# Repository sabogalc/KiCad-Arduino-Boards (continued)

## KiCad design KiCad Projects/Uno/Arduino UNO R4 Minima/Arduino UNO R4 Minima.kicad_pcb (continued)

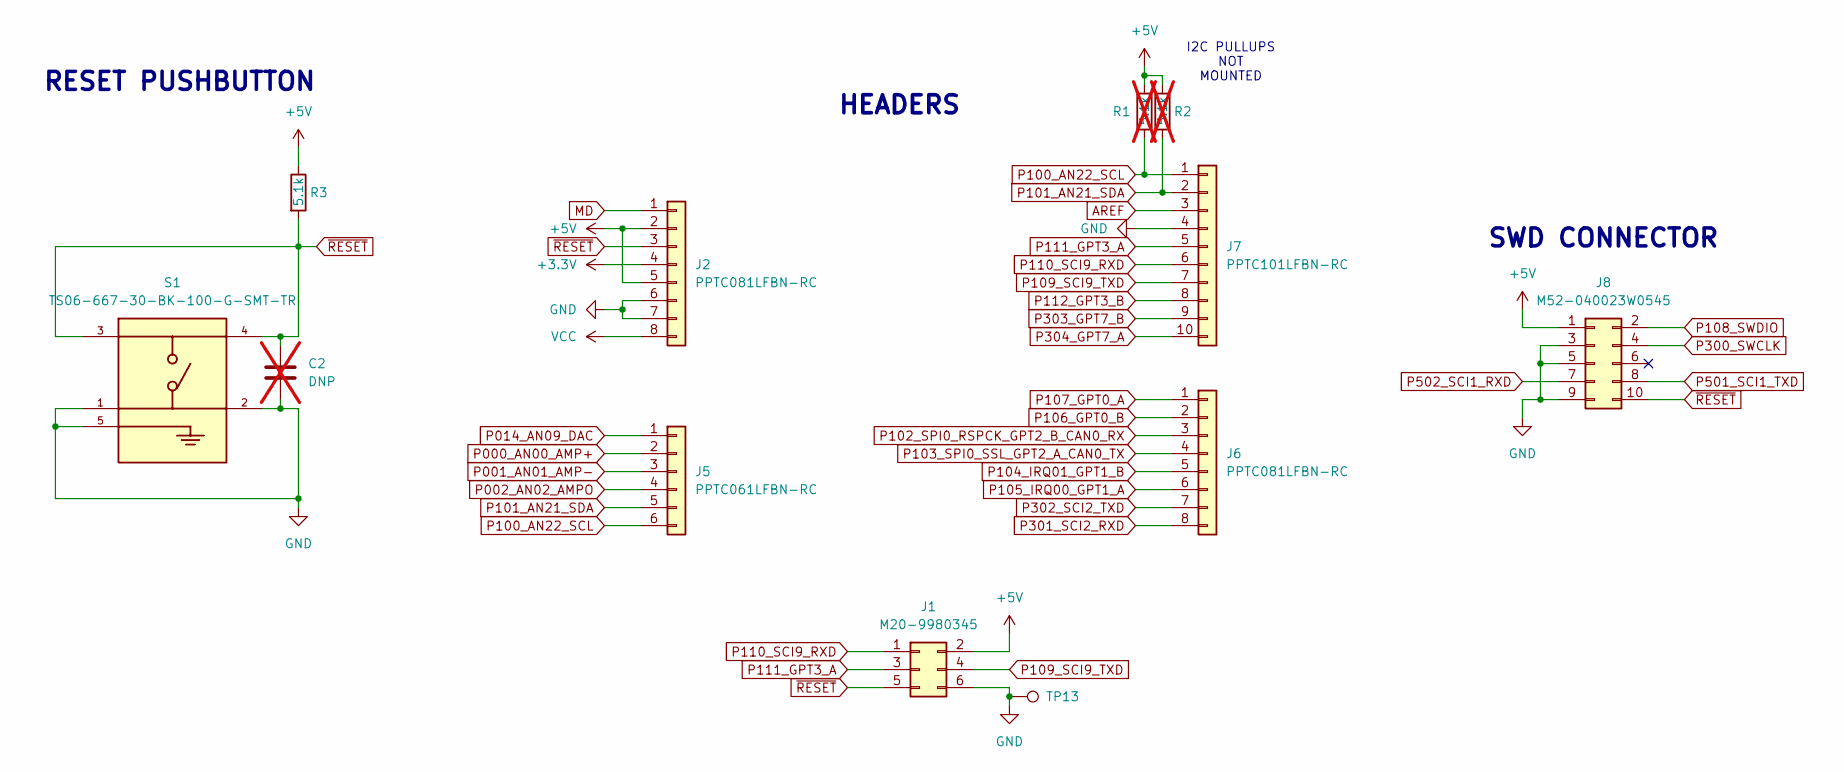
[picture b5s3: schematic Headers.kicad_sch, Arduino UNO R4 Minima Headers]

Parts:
C2: DNP; C_0402_1005Metric; not fitted
J1: M20-9980345; PinHeader_2x03_P2.54mm_Vertical
J2, J6: PPTC081LFBN-RC; PinSocket_1x08_P2.54mm_Vertical
J5: PPTC061LFBN-RC; PinSocket_1x06_P2.54mm_Vertical
J7: PPTC101LFBN-RC; PinSocket_1x10_P2.54mm_Vertical
J8: M52-040023W0545; PinHeader_2x05_P1.27mm_Vertical
R1, R2: 5.1k; R_0603_1608Metric; not fitted
R3: 5.1k; R_0402_1005Metric
S1: TS06-667-30-BK-100-G-SMT-TR; SW_TS06-667-30-BK-100-G-SMT-TR; PARTREV 1.0
TP13: TestPoint; TestPoint_Pad_D1.0mm

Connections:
+3.3V: J2.4; also elsewhere on the board
+5V: J1.2, J2.2, J2.5, J8.1, R1.1, R2.1, R3.1; also elsewhere on the board
AREF: J7.3; also elsewhere on the board
GND: C2.2, J1.6, J2.6, J2.7, J7.4, J8.3, J8.5, J8.9, S1.1, S1.2, S1.5, TP13.1; also elsewhere on the board
MD: J2.1; also elsewhere on the board
P000_AN00_AMP+: J5.2; also elsewhere on the board
P001_AN01_AMP-: J5.3; also elsewhere on the board
P002_AN02_AMPO: J5.4; also elsewhere on the board
P014_AN09_DAC: J5.1; also elsewhere on the board
P100_AN22_SCL: J5.6, J7.1, R1.2; also elsewhere on the board
P101_AN21_SDA: J5.5, J7.2, R2.2; also elsewhere on the board
P102_SPI0_RSPCK_GPT2_B_CAN0_RX: J6.3; also elsewhere on the board
P103_SPI0_SSL_GPT2_A_CAN0_TX: J6.4; also elsewhere on the board
P104_IRQ01_GPT1_B: J6.5; also elsewhere on the board
P105_IRQ00_GPT1_A: J6.6; also elsewhere on the board
P106_GPT0_B: J6.2; also elsewhere on the board
P107_GPT0_A: J6.1; also elsewhere on the board
P108_SWDIO: J8.2; also elsewhere on the board
P109_SCI9_TXD: J1.4, J7.7; also elsewhere on the board
P110_SCI9_RXD: J1.1, J7.6; also elsewhere on the board
P111_GPT3_A: J1.3, J7.5; also elsewhere on the board
P112_GPT3_B: J7.8; also elsewhere on the board
P300_SWCLK: J8.4; also elsewhere on the board
P301_SCI2_RXD: J6.8; also elsewhere on the board
P302_SCI2_TXD: J6.7; also elsewhere on the board
P303_GPT7_B: J7.9; also elsewhere on the board
P304_GPT7_A: J7.10; also elsewhere on the board
P501_SCI1_TXD: J8.8; also elsewhere on the board
P502_SCI1_RXD: J8.7; also elsewhere on the board
VCC: J2.8; also elsewhere on the board
~RESET: C2.1, J1.5, J2.3, J8.10, R3.2, S1.3, S1.4; also elsewhere on the board

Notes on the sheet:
RESET PUSHBUTTON
SWD CONNECTOR
HEADERS
I2C PULLUPS NOT MOUNTED

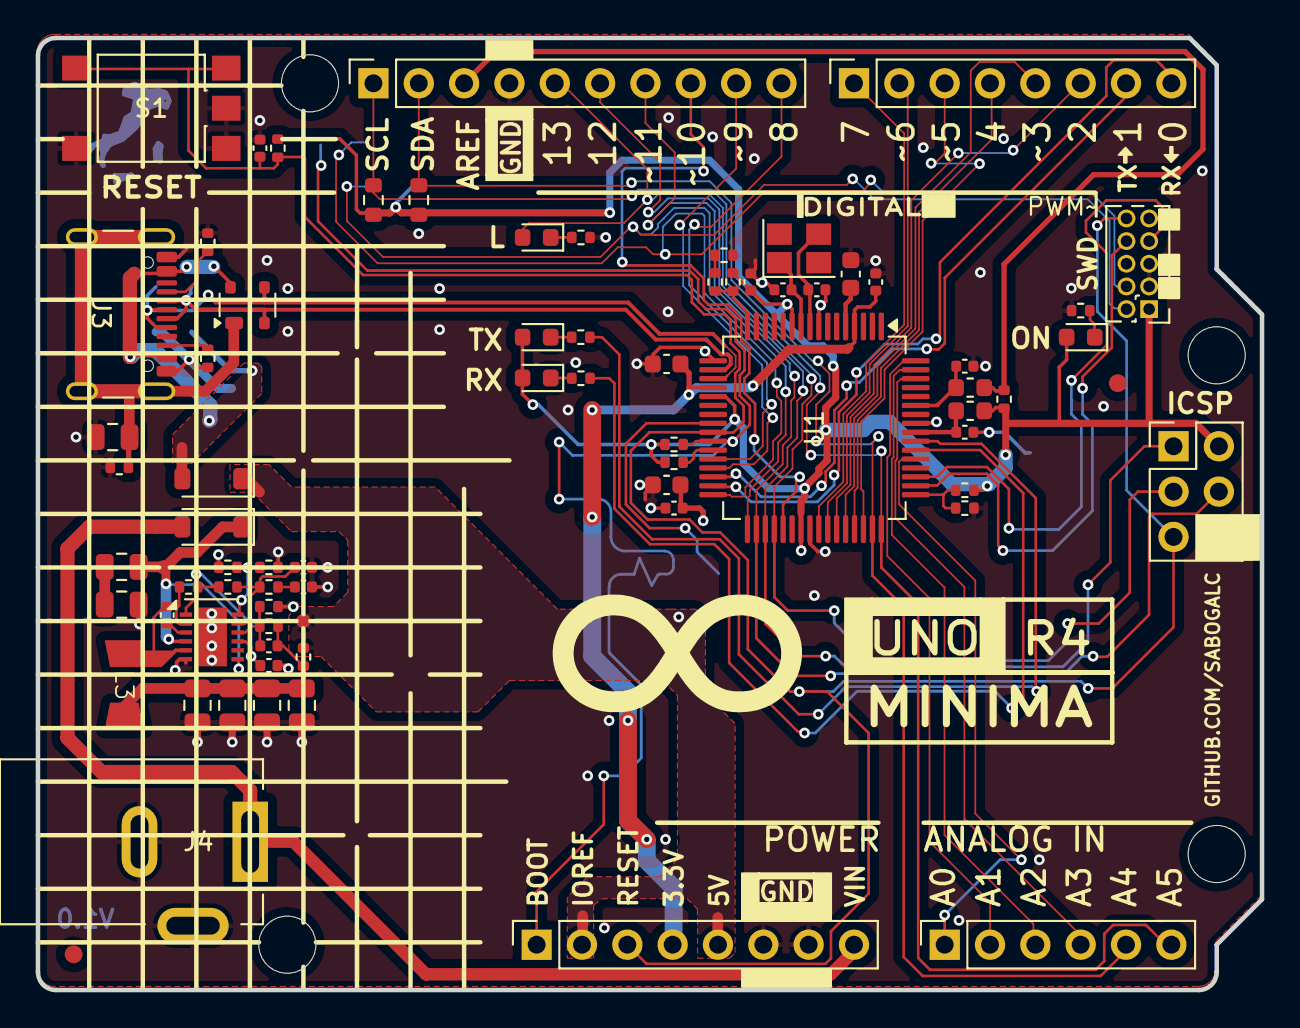
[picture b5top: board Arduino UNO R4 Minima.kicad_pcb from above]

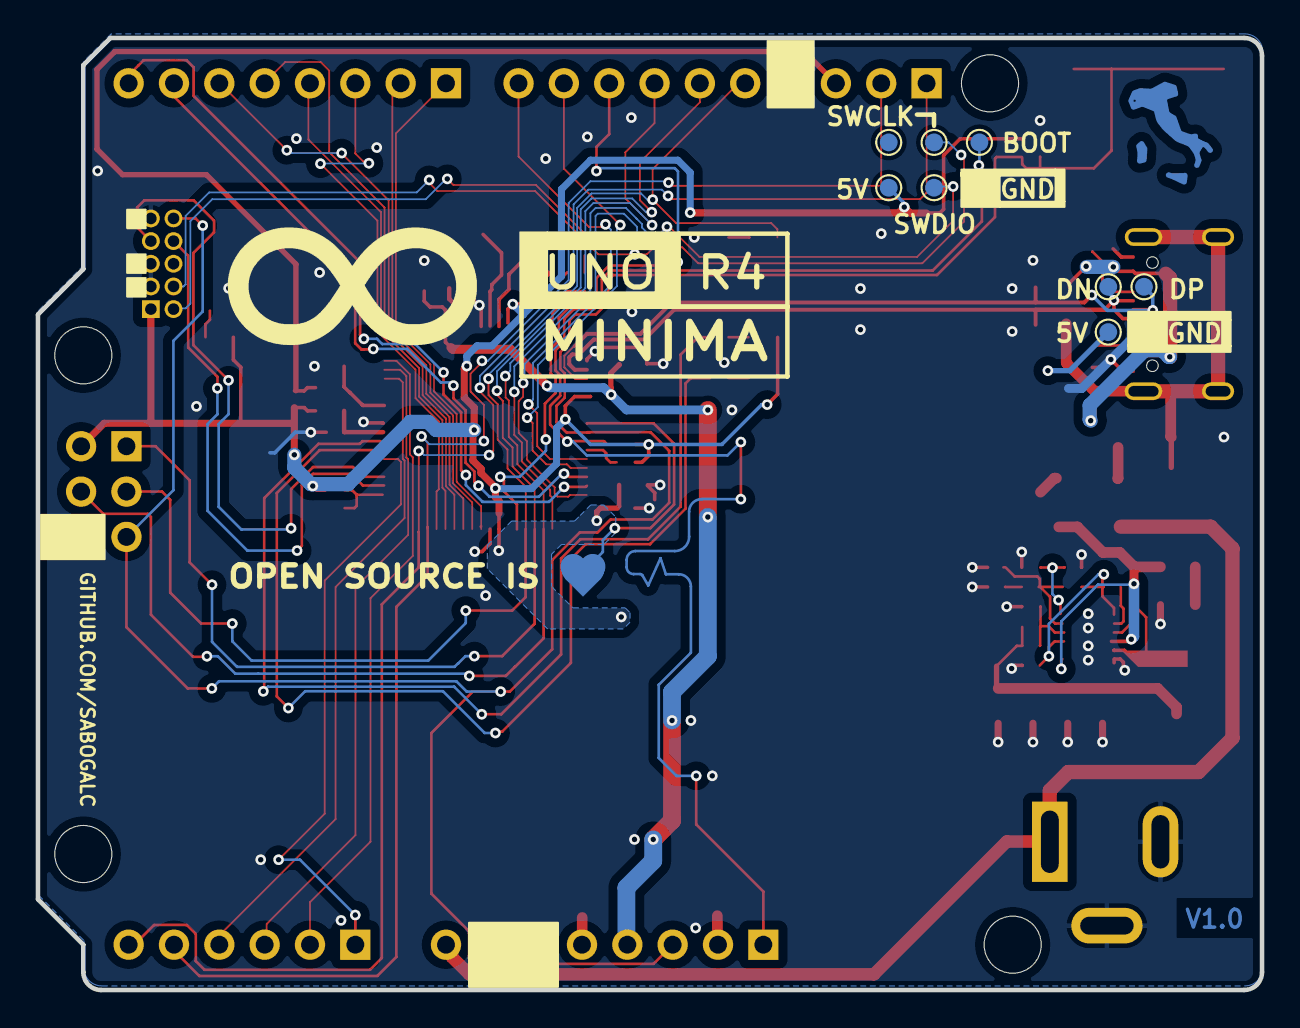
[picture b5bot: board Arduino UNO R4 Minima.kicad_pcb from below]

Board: 2 copper layers, 68.6 x 53.3 mm, 87 parts (11 on the bottom side), 64 nets.

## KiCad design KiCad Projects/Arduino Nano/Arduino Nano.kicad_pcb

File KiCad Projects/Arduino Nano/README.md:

# Nano

## Overview
The Nano is a compact and versatile board that surprisingly handles many of my existing projects designed for the UNO. Its small size makes it a great choice for projects where space is at a premium.

## Design Insights
This was the first board in this repository where I had to use a fully surface-mount USB-C connector instead of a through-hole variant. The original Nano also utilizes a surface-mount USB connector, as a through-hole option would interfere with routing and placement on the bottom layer.

While integrating the larger footprint of the USB-C connector, I had to adjust the silkscreen labels near the connector, but I ensured that all the necessary information remained clear and accessible.

## KiCad 3D View
Below are the screenshots of this board from KiCad's 3D board viewer.

## Real-World Application
Additionally, I have successfully built this board in real life and confirmed that it works.

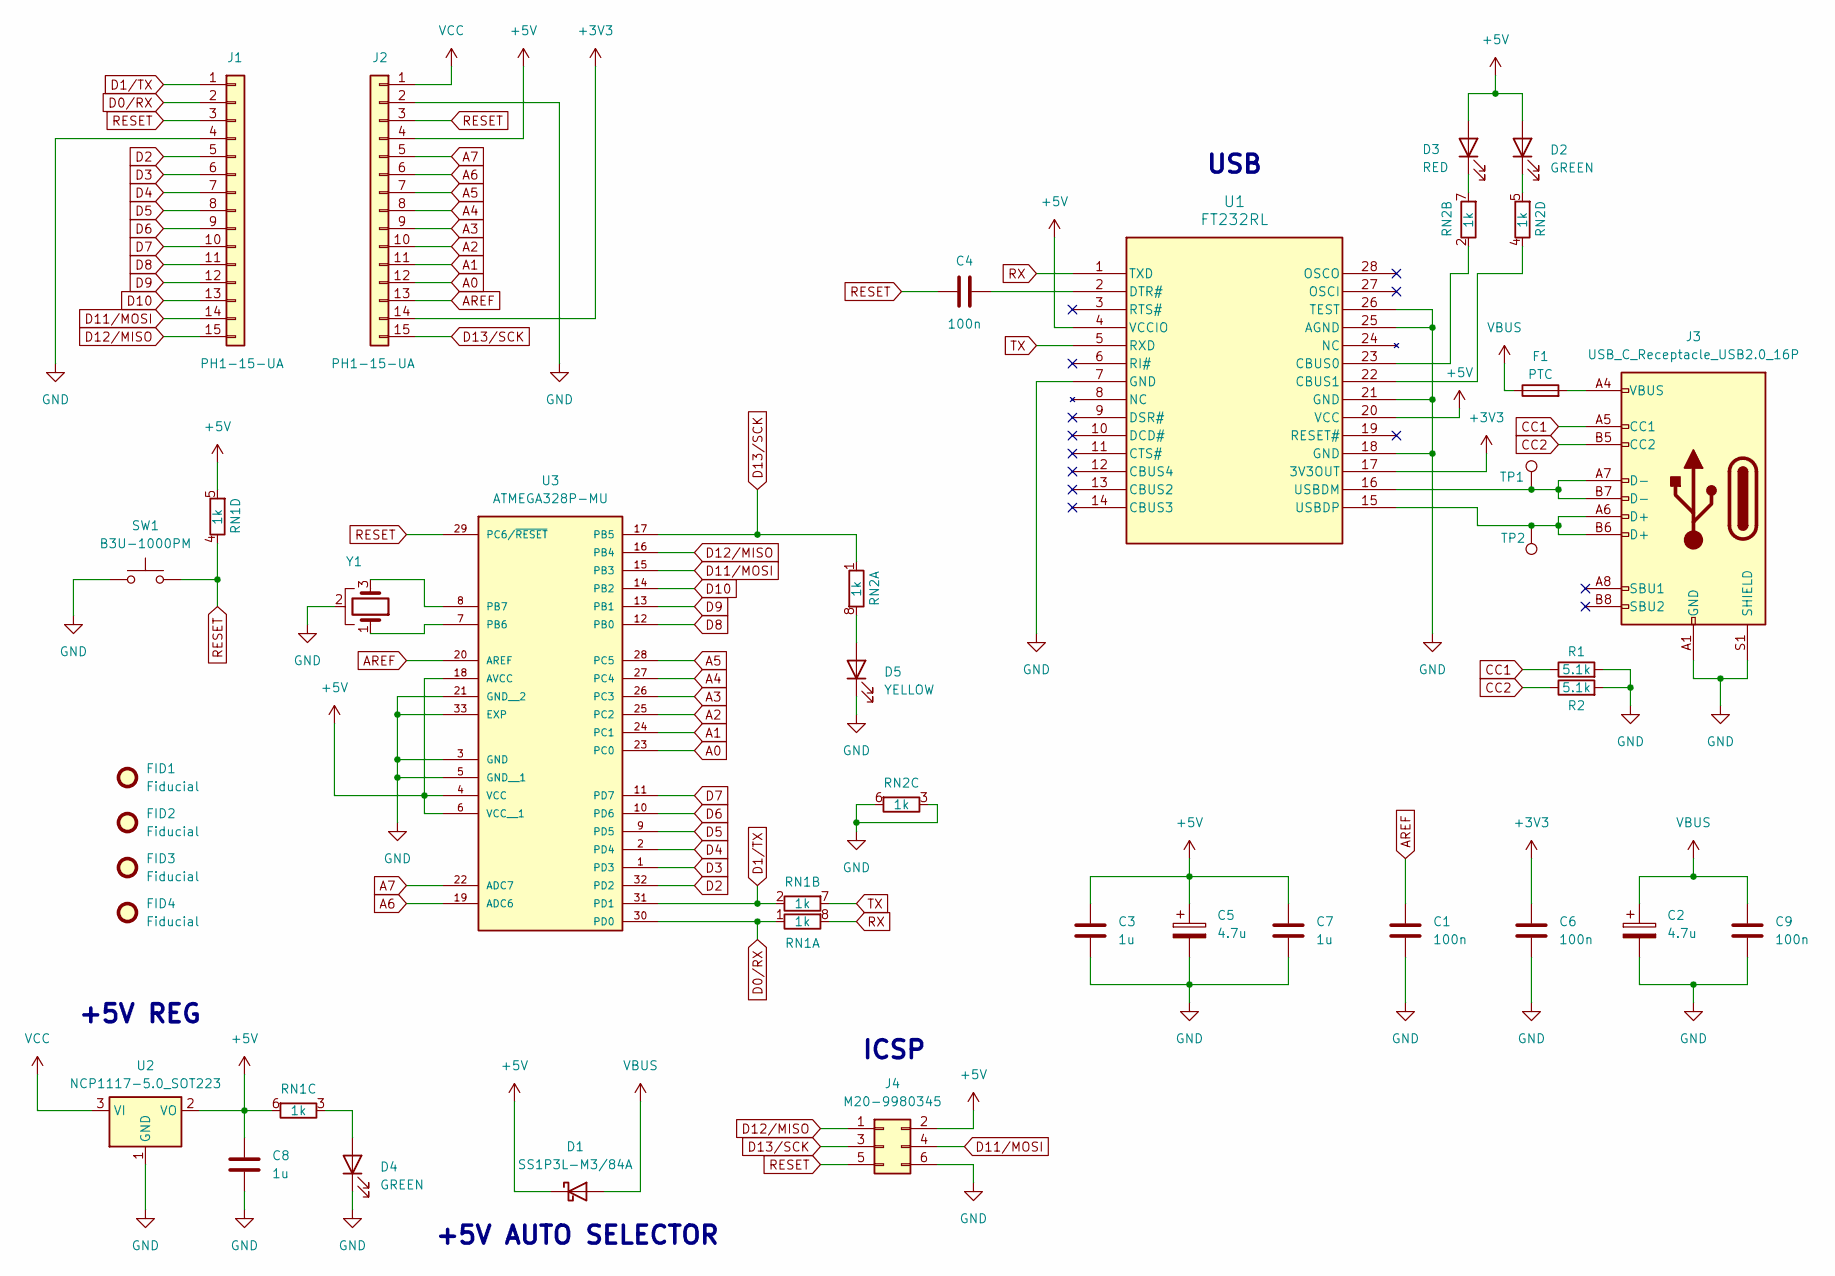
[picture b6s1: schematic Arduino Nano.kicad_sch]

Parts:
C1, C4, C6, C9: 100n; C_0603_1608Metric
C2, C5: 4.7u; CP_EIA-3216-10_Kemet-I
C3, C7, C8: 1u; C_0603_1608Metric
D1: SS1P3L-M3/84A; D_SMP_DO-220AA
D2, D4: GREEN; LED_0805_2012Metric
D3: RED; LED_0805_2012Metric
D5: YELLOW; LED_0805_2012Metric
F1: PTC; Fuse_0603_1608Metric
FID1, FID2, FID3, FID4: Fiducial; Fiducial_1mm_Mask2mm
J1, J2: PH1-15-UA; PinHeader_1x15_P2.54mm_Vertical
J3: USB_C_Receptacle_USB2.0_16P; USB_C_Receptacle_GCT_USB4110
J4: M20-9980345; PinHeader_2x03_P2.54mm_Vertical
R1, R2: 5.1k; R_0603_1608Metric
RN1, RN2: 1k; R_Array_Convex_4x0612
SW1: B3U-1000PM
TP1, TP2: TestPoint; TestPoint_Pad_D1.0mm
U1: FT232RL; SSOP-28_5.3x10.2mm_P0.65mm
U2: NCP1117-5.0_SOT223; SOT-223-3_TabPin2
U3: ATMEGA328P-MU; VQFN-32-1EP_5x5mm_P0.5mm_EP3.1x3.1mm
Y1: CSTNE16M0V530000R0; Resonator_SMD_Murata_CSTxExxV-3Pin_3.0x1.1mm

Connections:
+3V3: C6.2, J2.14, U1.17 (3V3OUT)
+5V: C3.1, C5.1, C7.1, C8.1, D1.1 (K), D2.2 (A), D3.2 (A), J2.4, J4.2, RN1.5 (R4.2), RN1.6 (R3.2), U1.4 (VCCIO), U1.20 (VCC), U2.2 (VO), U3.4 (VCC), U3.6 (VCC__1), U3.18 (AVCC)
A0: J2.12, U3.23 (PC0)
A1: J2.11, U3.24 (PC1)
A2: J2.10, U3.25 (PC2)
A3: J2.9, U3.26 (PC3)
A4: J2.8, U3.27 (PC4)
A5: J2.7, U3.28 (PC5)
A6: J2.6, U3.19 (ADC6)
A7: J2.5, U3.22 (ADC7)
AREF: C1.1, J2.13, U3.20 (AREF)
CC1: J3.A5 (CC1), R1.1
CC2: J3.B5 (CC2), R2.1
D0/RX: J1.2, RN1.1 (R1.1), U3.30 (PD0)
D1/TX: J1.1, RN1.2 (R2.1), U3.31 (PD1)
D2: J1.5, U3.32 (PD2)
D3: J1.6, U3.1 (PD3)
D4: J1.7, U3.2 (PD4)
D5: J1.8, U3.9 (PD5)
D6: J1.9, U3.10 (PD6)
D7: J1.10, U3.11 (PD7)
D8: J1.11, U3.12 (PB0)
D9: J1.12, U3.13 (PB1)
D10: J1.13, U3.14 (PB2)
D11/MOSI: J1.14, J4.4, U3.15 (PB3)
D12/MISO: J1.15, J4.1, U3.16 (PB4)
D13/SCK: J2.15, J4.3, RN2.1 (R1.1), U3.17 (PB5)
GND: C1.2, C2.2, C3.2, C5.2, C6.1, C7.2, C8.2, C9.2, D4.1 (K), D5.1 (K), J1.4, J2.2, J3.A1 (GND), J3.A12 (GND), J3.B1 (GND), J3.B12 (GND), J3.S1 (SHIELD), J4.6, R1.2, R2.2, RN2.3 (R3.1), RN2.6 (R3.2), SW1.1, U1.7 (GND), U1.18 (GND), U1.21 (GND), U1.25 (AGND), U1.26 (TEST), U2.1 (GND), U3.3 (GND), U3.5 (GND__1), U3.21 (GND__2), U3.33 (EXP), Y1.2
unnamed: D2.1 (K), RN2.5 (R4.2)
unnamed: D3.1 (K), RN2.7 (R2.2)
unnamed: D4.2 (A), RN1.3 (R3.1)
unnamed: D5.2 (A), RN2.8 (R1.2)
unnamed: F1.2, J3.A4 (VBUS), J3.A9 (VBUS), J3.B4 (VBUS), J3.B9 (VBUS)
unnamed: RN2.2 (R2.1), U1.23 (CBUS0)
unnamed: RN2.4 (R4.1), U1.22 (CBUS1)
unnamed: C4.2, U1.2 (DTR#)
unnamed: J3.A7 (D-), J3.B7 (D-), TP1.1, U1.16 (USBDM)
unnamed: J3.A6 (D+), J3.B6 (D+), TP2.1, U1.15 (USBDP)
unnamed: U3.7 (PB6), Y1.1
unnamed: U3.8 (PB7), Y1.3
RESET: C4.1, J1.3, J2.3, J4.5, RN1.4 (R4.1), SW1.2, U3.29 (PC6/~RESET)
RX: RN1.8 (R1.2), U1.1 (TXD)
TX: RN1.7 (R2.2), U1.5 (RXD)
VBUS: C2.1, C9.1, D1.2 (A), F1.1
VCC: J2.1, U2.3 (VI)

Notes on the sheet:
ICSP
USB
+5V AUTO SELECTOR
+5V REG

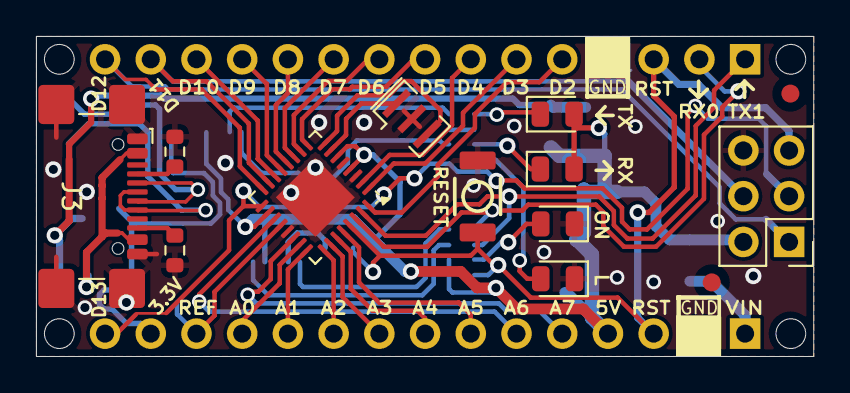
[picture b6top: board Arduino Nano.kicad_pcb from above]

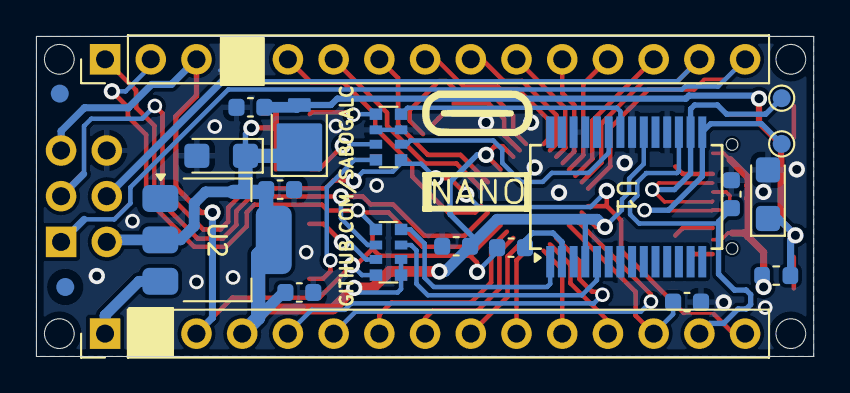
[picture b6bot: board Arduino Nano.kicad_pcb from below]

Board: 2 copper layers, 43.2 x 17.8 mm, 34 parts (21 on the bottom side), 45 nets.

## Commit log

2024-06-08 Initial Commit
    First commit containing KiCad projects and boardview files for the 8 boards.
2024-09-29 Added BOMs, updated READMEs
    Updated the READMEs for the Uno R4 Minima, Micro, and Nano to reflect that the boards have been confirmed to work in real life. Also added a README for the boardview files folder.
